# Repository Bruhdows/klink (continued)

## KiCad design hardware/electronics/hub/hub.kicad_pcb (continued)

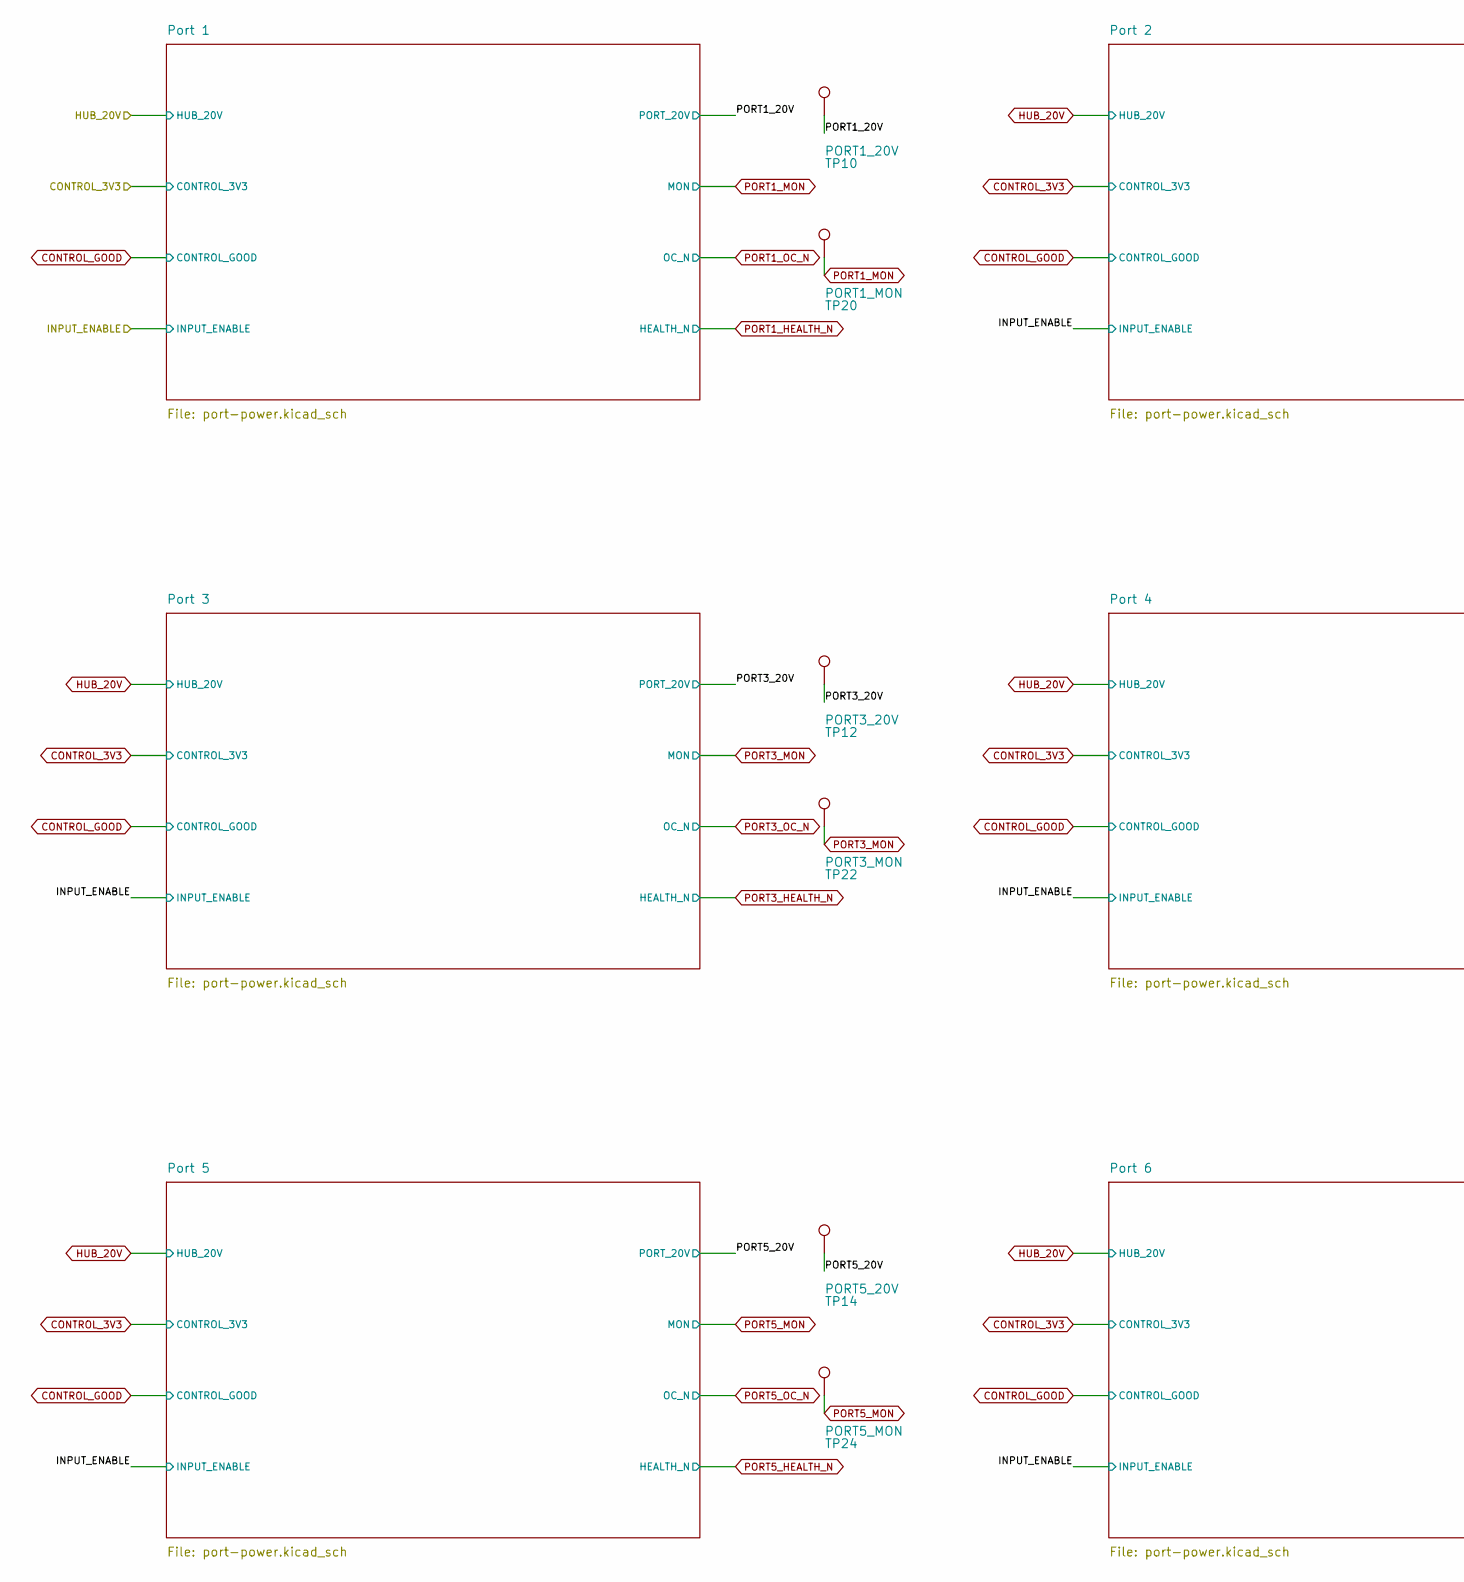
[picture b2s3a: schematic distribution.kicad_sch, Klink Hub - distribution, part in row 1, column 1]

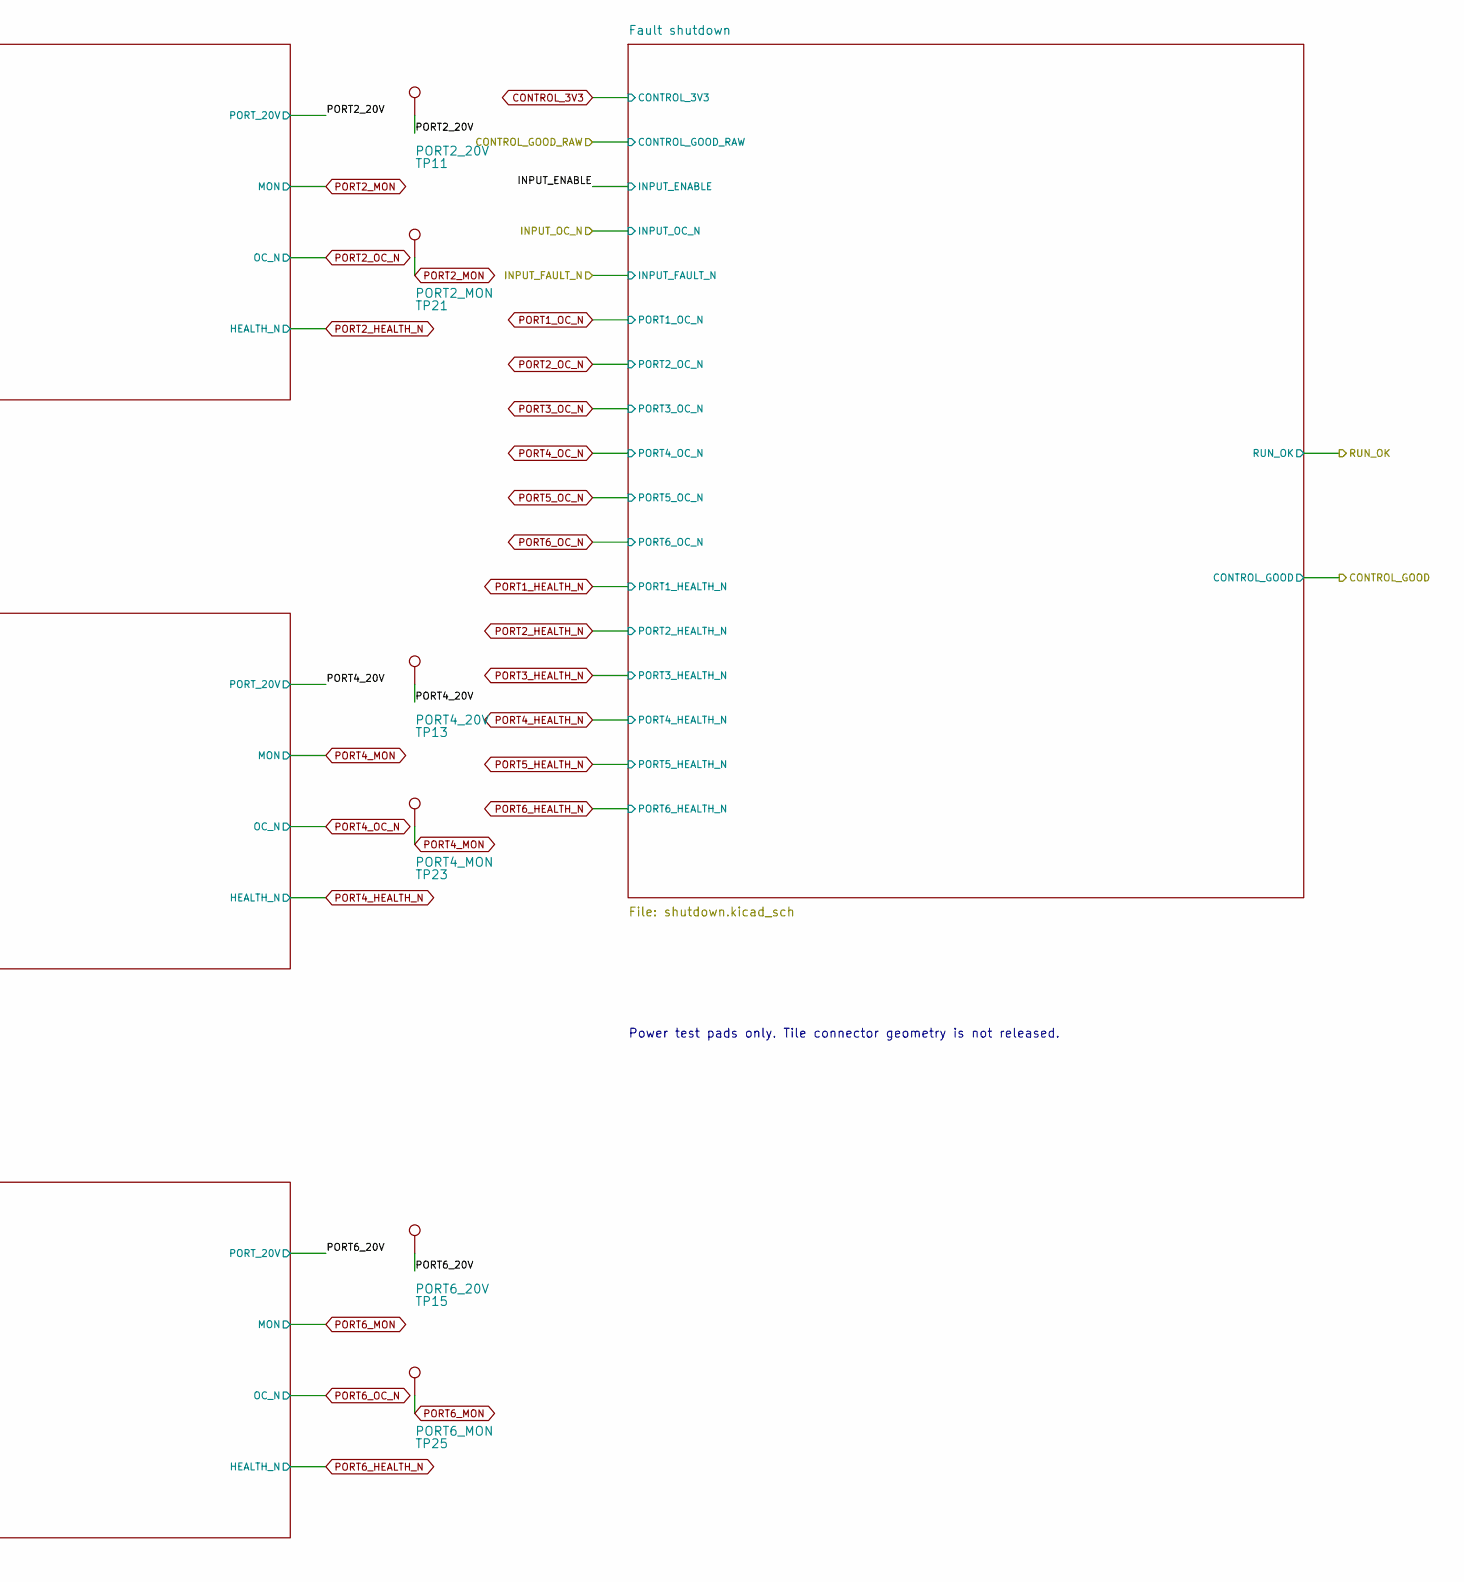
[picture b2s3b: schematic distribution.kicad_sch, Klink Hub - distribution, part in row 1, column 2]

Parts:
TP10: PORT1_20V; TestPoint_Pad_D2.0mm
TP11: PORT2_20V; TestPoint_Pad_D2.0mm
TP12: PORT3_20V; TestPoint_Pad_D2.0mm
TP13: PORT4_20V; TestPoint_Pad_D2.0mm
TP14: PORT5_20V; TestPoint_Pad_D2.0mm
TP15: PORT6_20V; TestPoint_Pad_D2.0mm
TP20: PORT1_MON; TestPoint_Pad_D2.0mm
TP21: PORT2_MON; TestPoint_Pad_D2.0mm
TP22: PORT3_MON; TestPoint_Pad_D2.0mm
TP23: PORT4_MON; TestPoint_Pad_D2.0mm
TP24: PORT5_MON; TestPoint_Pad_D2.0mm
TP25: PORT6_MON; TestPoint_Pad_D2.0mm

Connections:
/Distribution/PORT1_20V: TP10.1; also elsewhere on the board
/Distribution/PORT2_20V: TP11.1; also elsewhere on the board
/Distribution/PORT3_20V: TP12.1; also elsewhere on the board
/Distribution/PORT4_20V: TP13.1; also elsewhere on the board
/Distribution/PORT5_20V: TP14.1; also elsewhere on the board
/Distribution/PORT6_20V: TP15.1; also elsewhere on the board
PORT1_MON: TP20.1; also elsewhere on the board
PORT2_MON: TP21.1; also elsewhere on the board
PORT3_MON: TP22.1; also elsewhere on the board
PORT4_MON: TP23.1; also elsewhere on the board
PORT5_MON: TP24.1; also elsewhere on the board
PORT6_MON: TP25.1; also elsewhere on the board

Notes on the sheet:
Power test pads only. Tile connector geometry is not released.

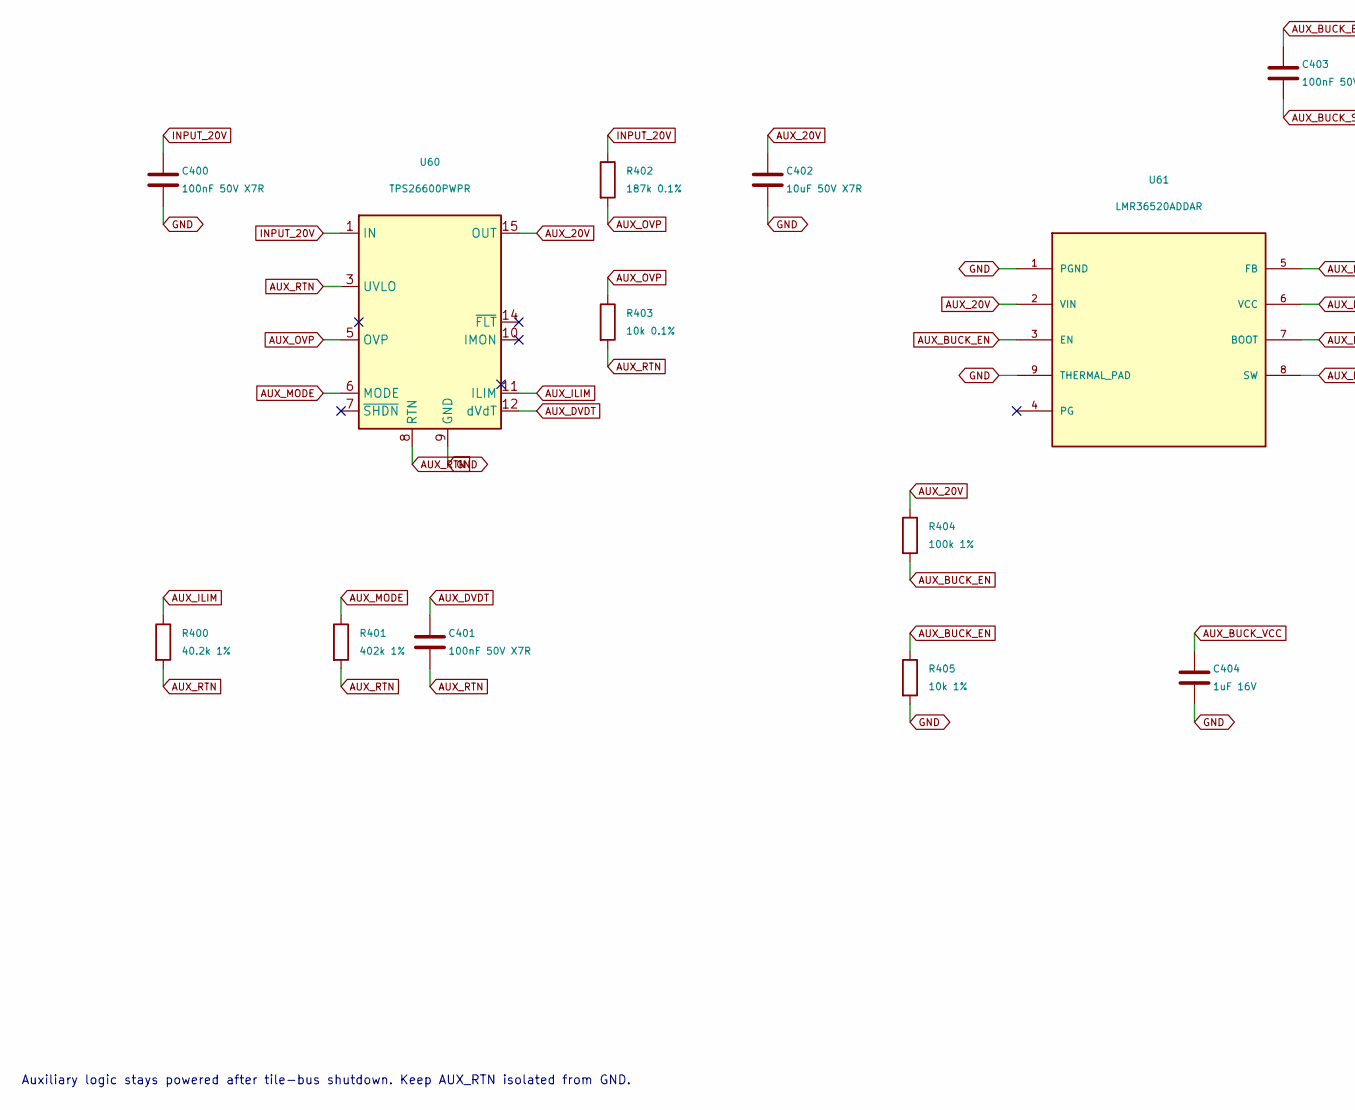
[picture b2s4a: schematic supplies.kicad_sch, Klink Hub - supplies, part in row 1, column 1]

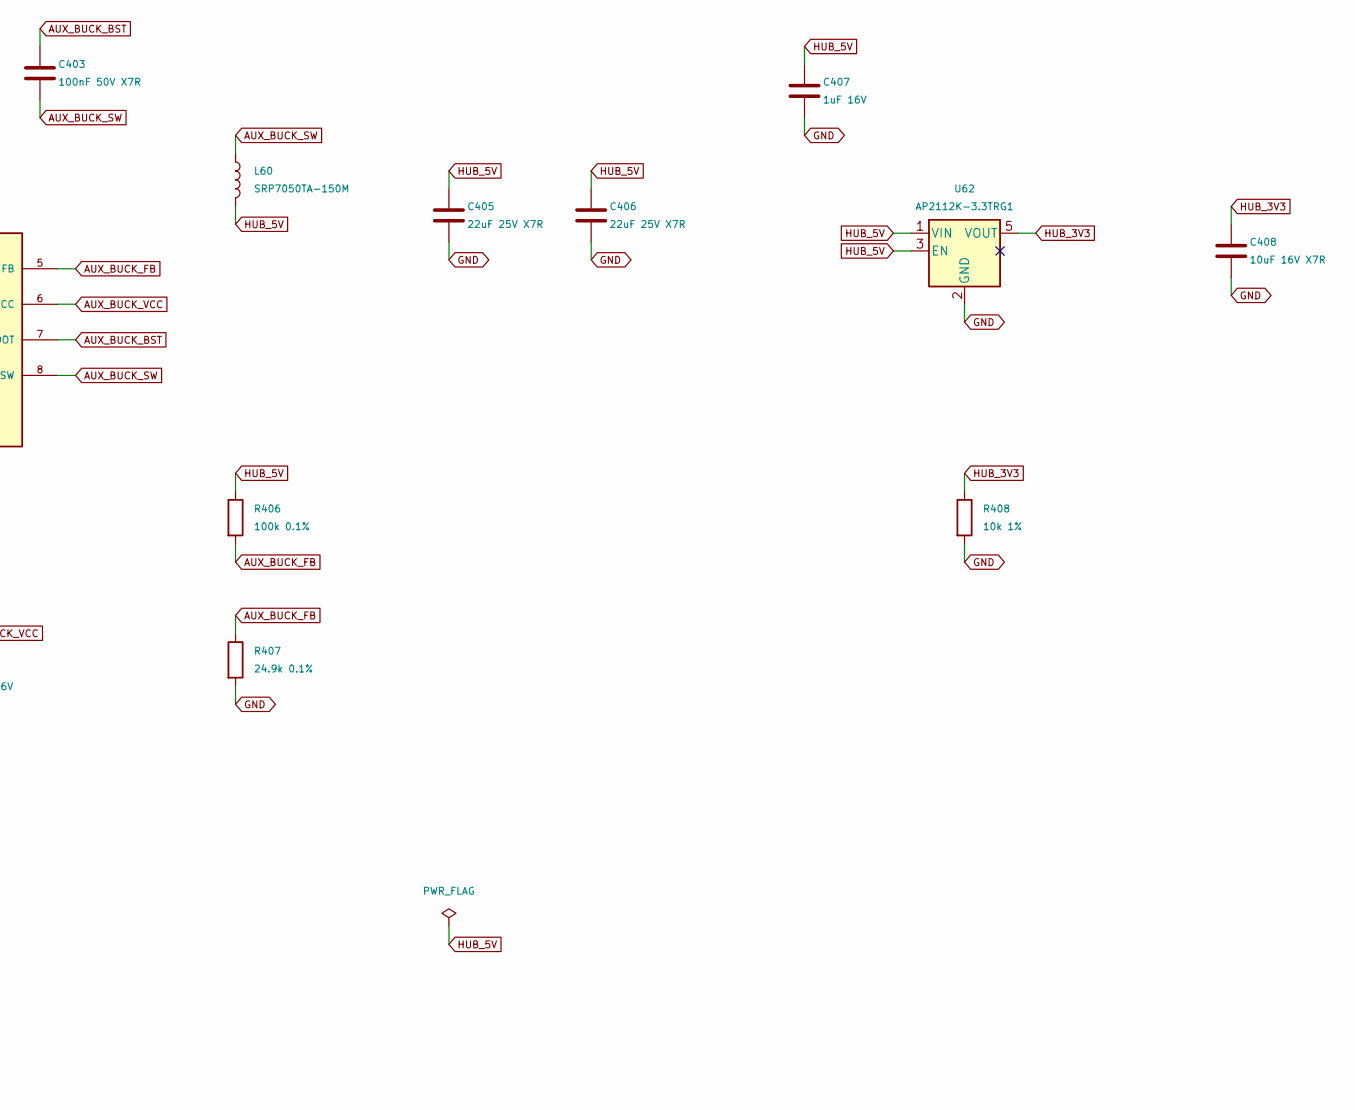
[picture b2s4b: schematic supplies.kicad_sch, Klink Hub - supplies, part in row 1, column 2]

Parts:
C400, C401, C403: 100nF 50V X7R; C_0805_2012Metric; MPN C2012X7R1H104K125AE
C402: 10uF 50V X7R; C_1206_3216Metric; MPN C3216X7R1H106K160AC
C404, C407: 1uF 16V; C_0805_2012Metric; MPN C2012X7R1H105K125AB
C405, C406: 22uF 25V X7R; C_1210_3225Metric; MPN C1210C226K3RACTU
C408: 10uF 16V X7R; C_1206_3216Metric; MPN C3216X7R1C106K160AC
L60: SRP7050TA-150M; L_Bourns_SRP7050TA; MPN SRP7050TA-150M
R400: 40.2k 1%; R_0805_2012Metric; MPN RC0805FR-0740K2L
R401: 402k 1%; R_0805_2012Metric; MPN RC0805FR-07402KL
R402: 187k 0.1%; R_0805_2012Metric; MPN RT0805BRD07187KL
R403: 10k 0.1%; R_0805_2012Metric; MPN RT0805BRD0710KL
R404: 100k 1%; R_0805_2012Metric; MPN RC0805FR-07100KL
R405, R408: 10k 1%; R_0805_2012Metric; MPN RC0805FR-0710KL
R406: 100k 0.1%; R_0805_2012Metric; MPN RT0805BRD07100KL
R407: 24.9k 0.1%; R_0805_2012Metric; MPN RT0805BRD0724K9L
U60: TPS26600PWPR; TI_PWP0016A_Mask3.3x3.3; MPN TPS26600PWPR
U61: LMR36520ADDAR; TI_SO-PowerPAD-8; MPN LMR36520ADDAR
U62: AP2112K-3.3TRG1; SOT-23-5; MPN AP2112K-3.3TRG1

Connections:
AUX_20V: C402.1, R404.1, U60.15 (OUT), U60.16 (OUT), U61.2 (VIN)
AUX_BUCK_BST: C403.1, U61.7 (BOOT)
AUX_BUCK_EN: R404.2, R405.1, U61.3 (EN)
AUX_BUCK_FB: R406.2, R407.1, U61.5 (FB)
AUX_BUCK_SW: C403.2, L60.1, U61.8 (SW)
AUX_BUCK_VCC: C404.1, U61.6 (VCC)
AUX_DVDT: C401.1, U60.12 (dVdT)
AUX_ILIM: R400.1, U60.11 (ILIM)
AUX_MODE: R401.1, U60.6 (MODE)
AUX_OVP: R402.2, R403.1, U60.5 (OVP)
AUX_RTN: C401.2, R400.2, R401.2, R403.2, U60.3 (UVLO), U60.8 (RTN), U60.17 (RTN)
GND: C400.2, C402.2, C404.2, C405.2, C406.2, C407.2, C408.2, R405.2, R407.2, R408.2, U60.9 (GND), U61.1 (PGND), U61.9 (THERMAL_PAD), U62.2 (GND); also elsewhere on the board
HUB_3V3: C408.1, R408.1, U62.5 (VOUT); also elsewhere on the board
HUB_5V: C405.1, C406.1, C407.1, L60.2, R406.1, U62.1 (VIN), U62.3 (EN); also elsewhere on the board
INPUT_20V: C400.1, R402.1, U60.1 (IN), U60.2 (IN); also elsewhere on the board

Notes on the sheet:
Auxiliary logic stays powered after tile-bus shutdown. Keep AUX_RTN isolated from GND.

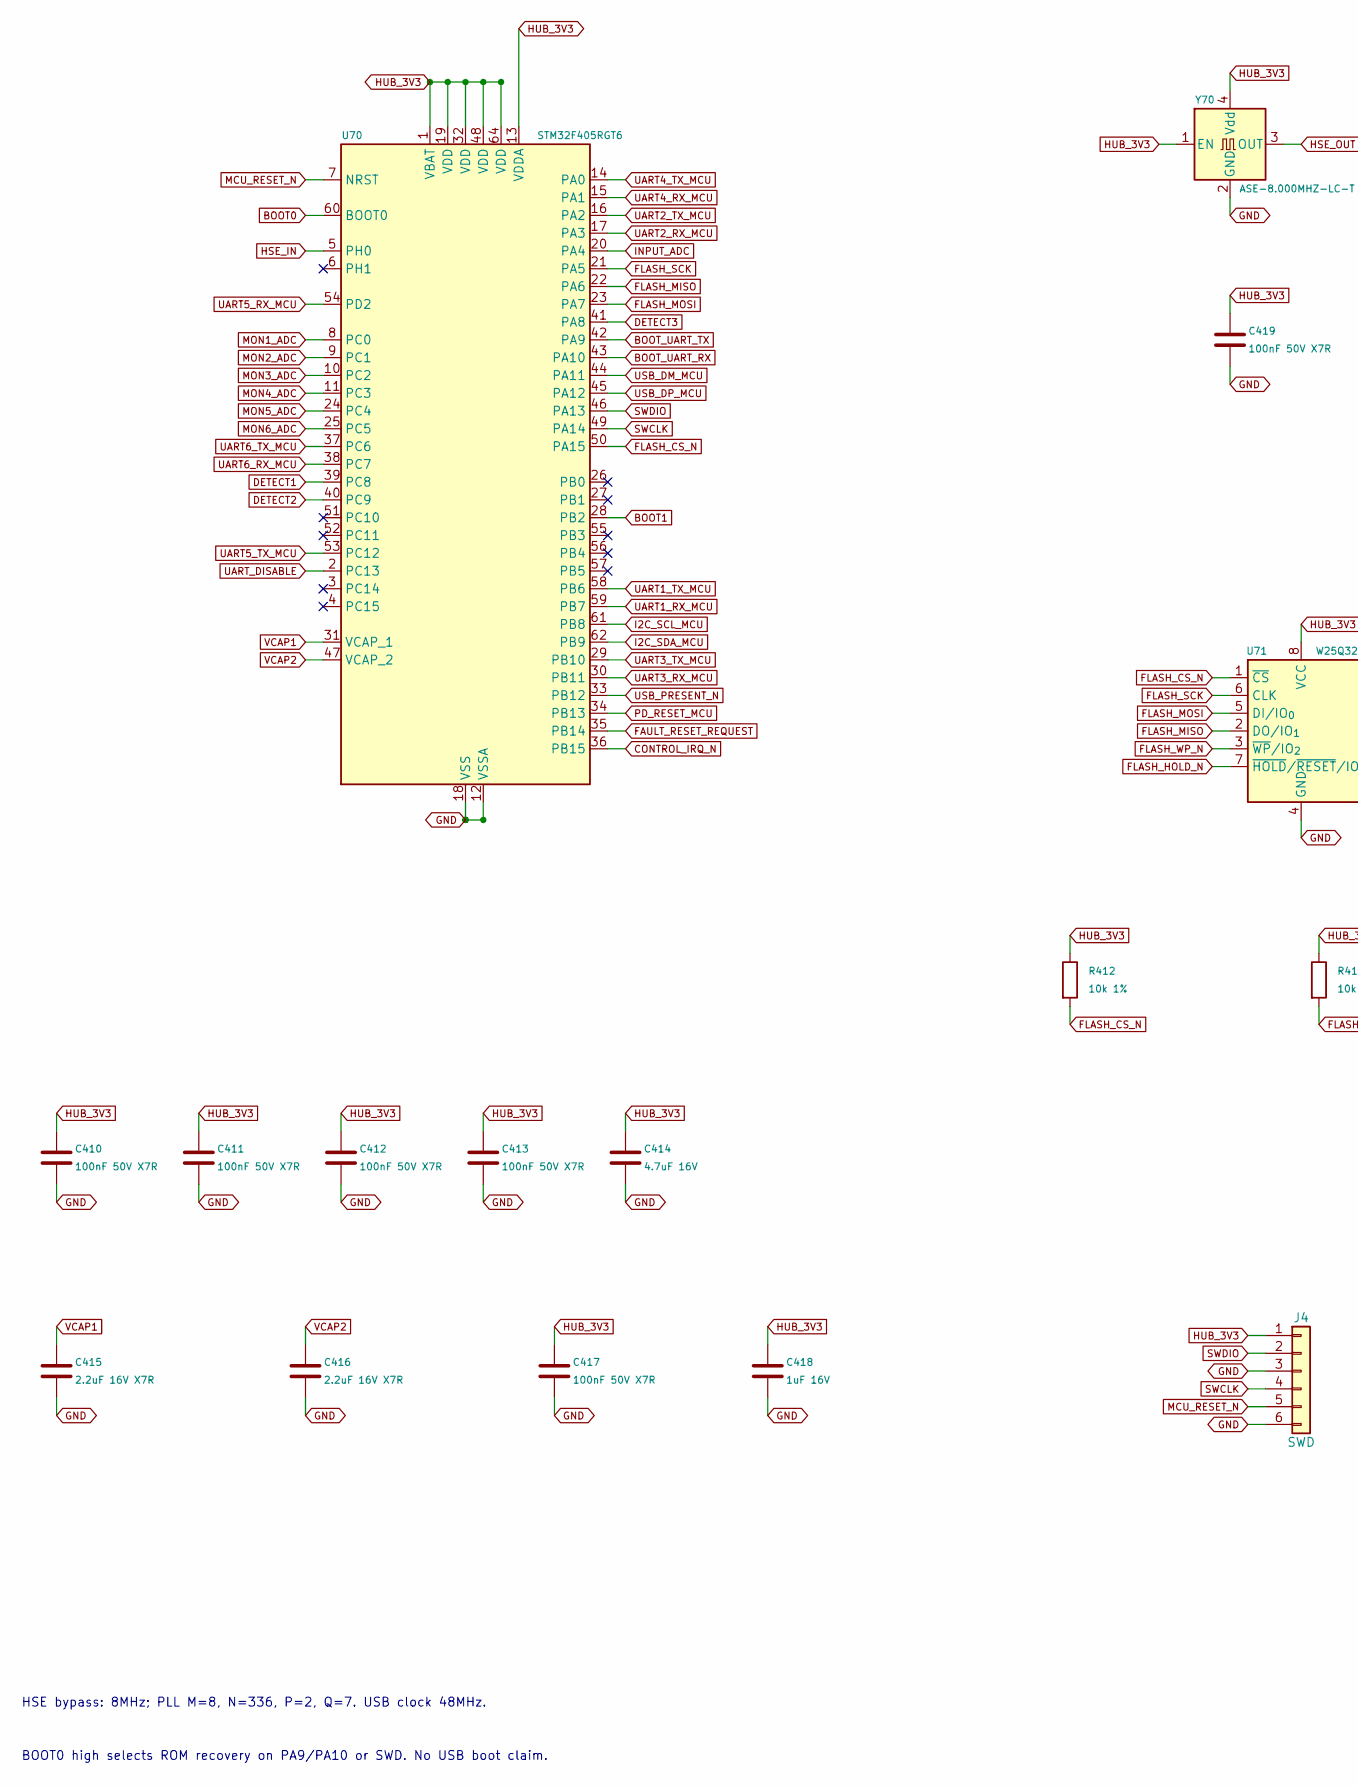
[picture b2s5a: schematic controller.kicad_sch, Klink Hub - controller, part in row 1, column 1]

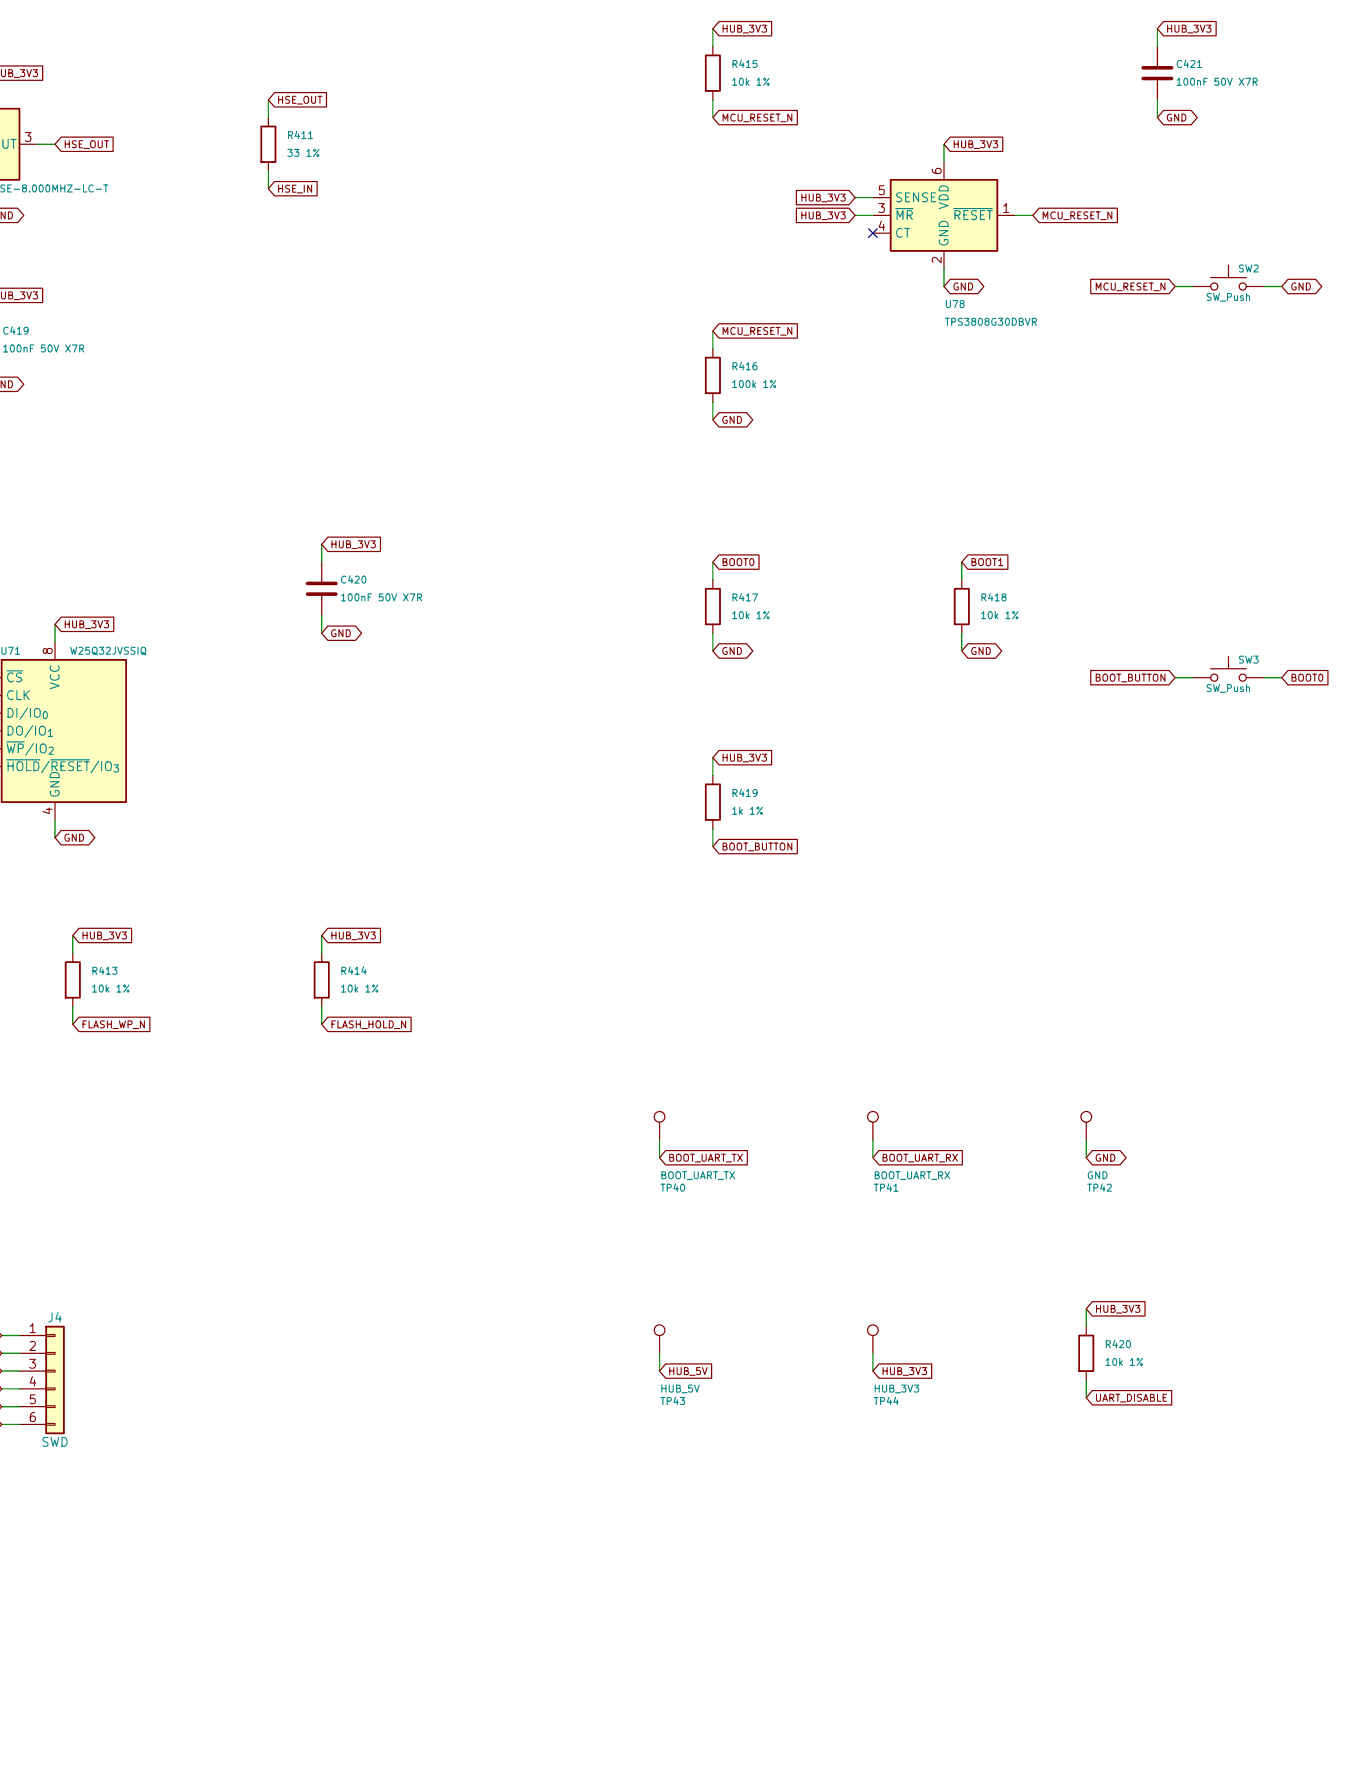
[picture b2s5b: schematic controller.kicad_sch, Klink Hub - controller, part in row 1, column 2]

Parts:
C410, C411, C412, C413, C417, C419, C420, C421: 100nF 50V X7R; C_0805_2012Metric; MPN C2012X7R1H104K125AE
C414: 4.7uF 16V; C_0805_2012Metric; MPN C2012X7R1C475K125AB
C415, C416: 2.2uF 16V X7R; C_0805_2012Metric; MPN C2012X7R1C225K125AB
C418: 1uF 16V; C_0805_2012Metric; MPN C2012X7R1H105K125AB
J4: SWD; PinHeader_1x06_P2.54mm_Vertical; MPN TSW-106-07-G-S
R411: 33 1%; R_0805_2012Metric; MPN RC0805FR-0733RL
R412, R413, R414, R415, R417, R418, R420: 10k 1%; R_0805_2012Metric; MPN RC0805FR-0710KL
R416: 100k 1%; R_0805_2012Metric; MPN RC0805FR-07100KL
R419: 1k 1%; R_0805_2012Metric; MPN RC0805FR-071KL
SW2, SW3: SW_Push; SW_SPST_B3U-1000P; MPN B3U-1000P
TP40: BOOT_UART_TX; TestPoint_Pad_D2.0mm
TP41: BOOT_UART_RX; TestPoint_Pad_D2.0mm
TP42: GND; TestPoint_Pad_D2.0mm
TP43: HUB_5V; TestPoint_Pad_D2.0mm
TP44: HUB_3V3; TestPoint_Pad_D2.0mm
U70: STM32F405RGT6; LQFP-64_10x10mm_P0.5mm; MPN STM32F405RGT6
U71: W25Q32JVSSIQ; SOIC-8_5.3x5.3mm_P1.27mm; MPN W25Q32JVSSIQ
U78: TPS3808G30DBVR; SOT-23-6; MPN TPS3808G30DBVR
Y70: ASE-8.000MHZ-LC-T; Oscillator_SMD_Abracon_ASE-4Pin_3.2x2.5mm; MPN ASE-8.000MHZ-LC-T

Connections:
BOOT0: R417.1, SW3.2, U70.60 (BOOT0)
BOOT1: R418.1, U70.28 (PB2)
BOOT_BUTTON: R419.2, SW3.1
BOOT_UART_RX: TP41.1, U70.43 (PA10)
BOOT_UART_TX: TP40.1, U70.42 (PA9)
CONTROL_IRQ_N: U70.36 (PB15); also elsewhere on the board
DETECT1: U70.39 (PC8); also elsewhere on the board
DETECT2: U70.40 (PC9); also elsewhere on the board
DETECT3: U70.41 (PA8); also elsewhere on the board
FAULT_RESET_REQUEST: U70.35 (PB14); also elsewhere on the board
FLASH_CS_N: R412.2, U70.50 (PA15), U71.1 (~CS)
FLASH_HOLD_N: R414.2, U71.7 (~HOLD/~RESET/IO_{3})
FLASH_MISO: U70.22 (PA6), U71.2 (DO/IO_{1})
FLASH_MOSI: U70.23 (PA7), U71.5 (DI/IO_{0})
FLASH_SCK: U70.21 (PA5), U71.6 (CLK)
FLASH_WP_N: R413.2, U71.3 (~WP/IO_{2})
GND: C410.2, C411.2, C412.2, C413.2, C414.2, C415.2, C416.2, C417.2, C418.2, C419.2, C420.2, C421.2, J4.3, J4.6, R416.2, R417.2, R418.2, SW2.2, TP42.1, U70.12 (VSSA), U70.18 (VSS), U70.63 (VSS), U71.4 (GND), U78.2 (GND), Y70.2 (GND); also elsewhere on the board
HSE_IN: R411.2, U70.5 (PH0)
HSE_OUT: R411.1, Y70.3 (OUT)
HUB_3V3: C410.1, C411.1, C412.1, C413.1, C414.1, C417.1, C418.1, C419.1, C420.1, C421.1, J4.1, R412.1, R413.1, R414.1, R415.1, R419.1, R420.1, TP44.1, U70.1 (VBAT), U70.13 (VDDA), U70.19 (VDD), U70.32 (VDD), U70.48 (VDD), U70.64 (VDD), U71.8 (VCC), U78.3 (~MR), U78.5 (SENSE), U78.6 (VDD), Y70.1 (EN), Y70.4 (Vdd); also elsewhere on the board
HUB_5V: TP43.1; also elsewhere on the board
I2C_SCL_MCU: U70.61 (PB8); also elsewhere on the board
I2C_SDA_MCU: U70.62 (PB9); also elsewhere on the board
INPUT_ADC: U70.20 (PA4); also elsewhere on the board
MCU_RESET_N: J4.5, R415.2, R416.1, SW2.1, U70.7 (NRST), U78.1 (~RESET); also elsewhere on the board
MON1_ADC: U70.8 (PC0); also elsewhere on the board
MON2_ADC: U70.9 (PC1); also elsewhere on the board
MON3_ADC: U70.10 (PC2); also elsewhere on the board
MON4_ADC: U70.11 (PC3); also elsewhere on the board
MON5_ADC: U70.24 (PC4); also elsewhere on the board
MON6_ADC: U70.25 (PC5); also elsewhere on the board
PD_RESET_MCU: U70.34 (PB13); also elsewhere on the board
SWCLK: J4.4, U70.49 (PA14)
SWDIO: J4.2, U70.46 (PA13)
UART1_RX_MCU: U70.59 (PB7); also elsewhere on the board
UART1_TX_MCU: U70.58 (PB6); also elsewhere on the board
UART2_RX_MCU: U70.17 (PA3); also elsewhere on the board
UART2_TX_MCU: U70.16 (PA2); also elsewhere on the board
UART3_RX_MCU: U70.30 (PB11); also elsewhere on the board
UART3_TX_MCU: U70.29 (PB10); also elsewhere on the board
UART4_RX_MCU: U70.15 (PA1); also elsewhere on the board
UART4_TX_MCU: U70.14 (PA0); also elsewhere on the board
UART5_RX_MCU: U70.54 (PD2); also elsewhere on the board
UART5_TX_MCU: U70.53 (PC12); also elsewhere on the board
UART6_RX_MCU: U70.38 (PC7); also elsewhere on the board
UART6_TX_MCU: U70.37 (PC6); also elsewhere on the board
UART_DISABLE: R420.2, U70.2 (PC13); also elsewhere on the board
USB_DM_MCU: U70.44 (PA11); also elsewhere on the board
USB_DP_MCU: U70.45 (PA12); also elsewhere on the board
USB_PRESENT_N: U70.33 (PB12); also elsewhere on the board
VCAP1: C415.1, U70.31 (VCAP_1)
VCAP2: C416.1, U70.47 (VCAP_2)

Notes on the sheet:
HSE bypass: 8MHz; PLL M=8, N=336, P=2, Q=7. USB clock 48MHz.
BOOT0 high selects ROM recovery on PA9/PA10 or SWD. No USB boot claim.
